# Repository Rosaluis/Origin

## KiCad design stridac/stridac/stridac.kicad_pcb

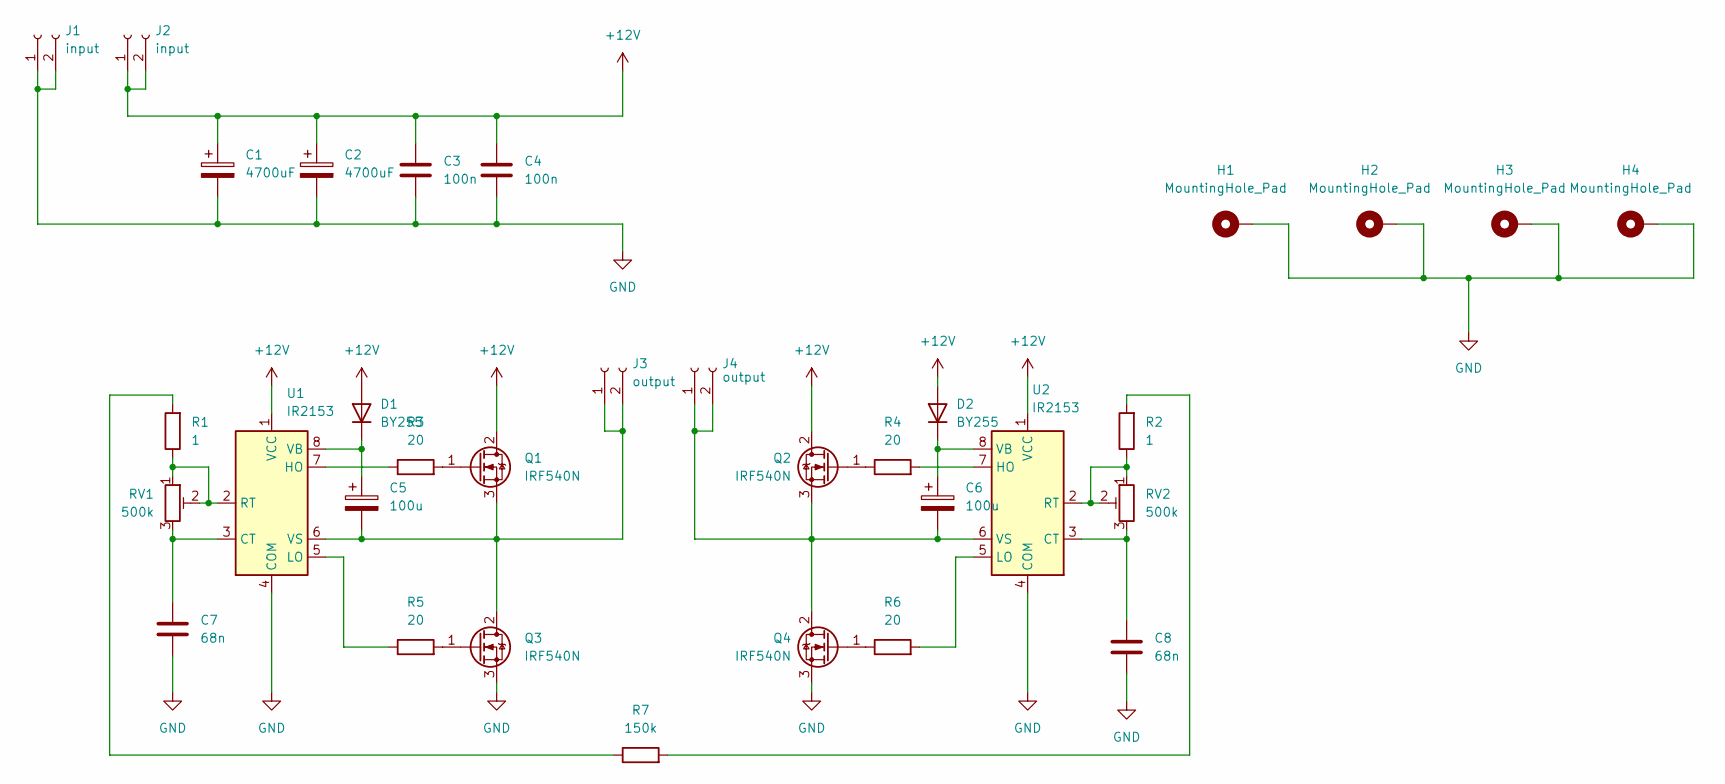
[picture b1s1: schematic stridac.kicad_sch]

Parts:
C1, C2: 4700uF; CP_Radial_D17.0mm_P7.50mm
C3, C4: 100n; C_1206_3216Metric_Pad1.33x1.80mm_HandSolder
C5, C6: 100u; CP_Radial_D8.0mm_P3.50mm
C7, C8: 68n; C_0805_2012Metric_Pad1.18x1.45mm_HandSolder
D1, D2: BY255; D_A-405_P10.16mm_Horizontal
H1, H2, H3, H4: MountingHole_Pad; MountingHole_3.2mm_M3_DIN965_Pad
J1, J2: input; PinHeader_1x02_P2.54mm_Vertical
J3, J4: output; PinHeader_1x02_P2.54mm_Vertical
Q1, Q2, Q3, Q4: IRF540N; TO-220-3_Vertical
R1, R2: 1; R_1206
R3, R4, R5, R6: 20; R_1206
R7: 150k; R_1206
RV1, RV2: 500k; Potentiometer_Vishay_T73XW_Horizontal
U1, U2: IR2153; DIP-8_W7.62mm

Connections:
+12V: C1.1, C2.1, C3.1, C4.1, D1.2 (A), D2.2 (A), J2.1, J2.2, Q1.2 (D), Q2.2 (D), U1.1 (VCC), U2.1 (VCC)
GND: C1.2, C2.2, C3.2, C4.2, C7.2, C8.2, H1.1, H2.1, H3.1, H4.1, J1.1, J1.2, Q3.3 (S), Q4.3 (S), U1.4 (COM), U2.4 (COM)
unnamed: C5.1, D1.1 (K), U1.8 (VB)
unnamed: C5.2, J3.1, J3.2, Q1.3 (S), Q3.2 (D), U1.6 (VS)
unnamed: C6.1, D2.1 (K), U2.8 (VB)
unnamed: C6.2, J4.1, J4.2, Q2.3 (S), Q4.2 (D), U2.6 (VS)
unnamed: C7.1, RV1.3, U1.3 (CT)
unnamed: C8.1, RV2.3, U2.3 (CT)
unnamed: Q1.1 (G), R3.2
unnamed: Q2.1 (G), R4.1
unnamed: Q3.1 (G), R5.2
unnamed: Q4.1 (G), R6.1
unnamed: R1.1, RV1.1, RV1.2, U1.2 (RT)
unnamed: R1.2, R7.1
unnamed: R2.1, RV2.1, RV2.2, U2.2 (RT)
unnamed: R2.2, R7.2
unnamed: R3.1, U1.7 (HO)
unnamed: R4.2, U2.7 (HO)
unnamed: R5.1, U1.5 (LO)
unnamed: R6.2, U2.5 (LO)

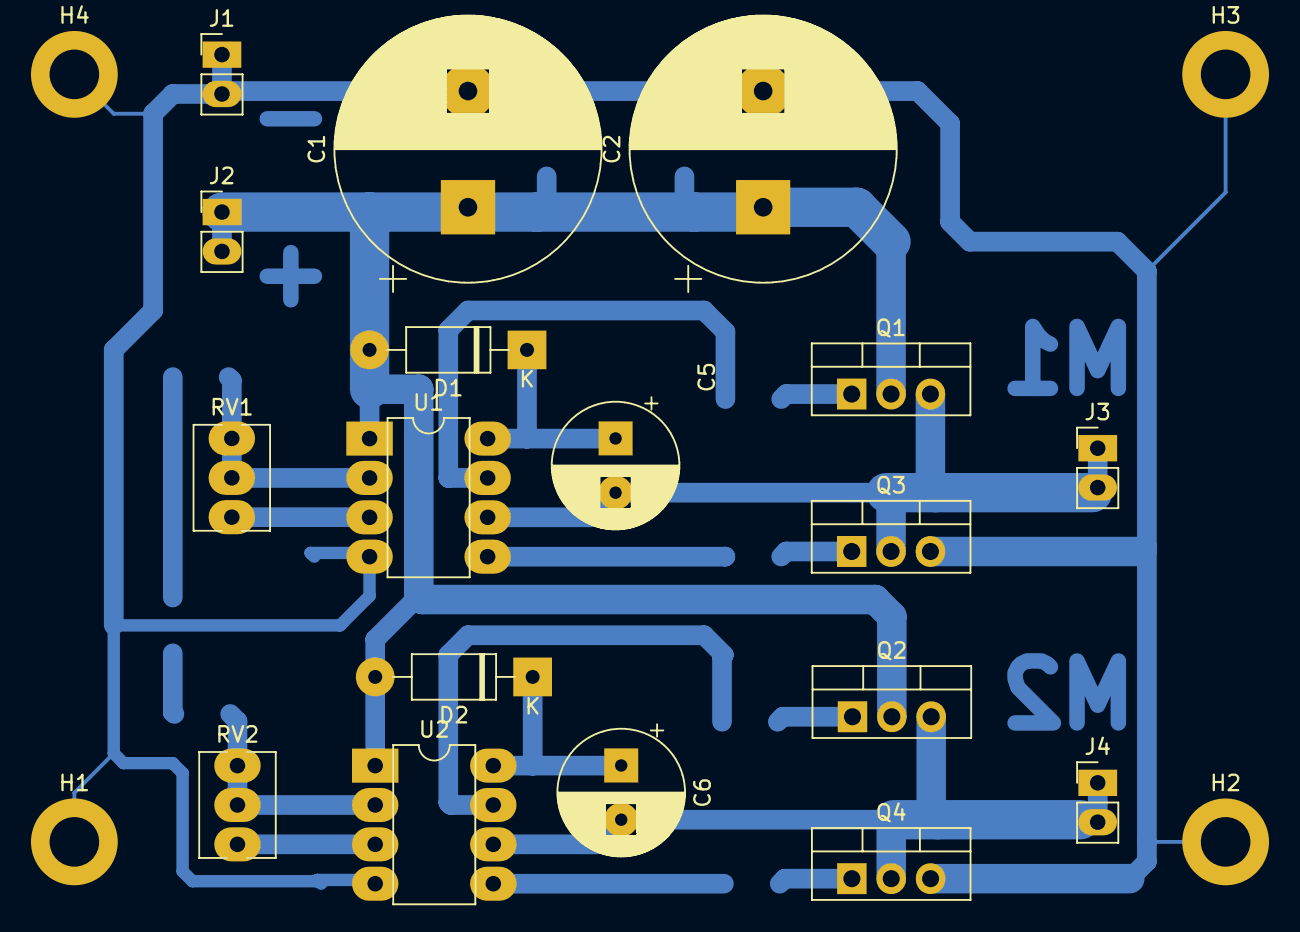
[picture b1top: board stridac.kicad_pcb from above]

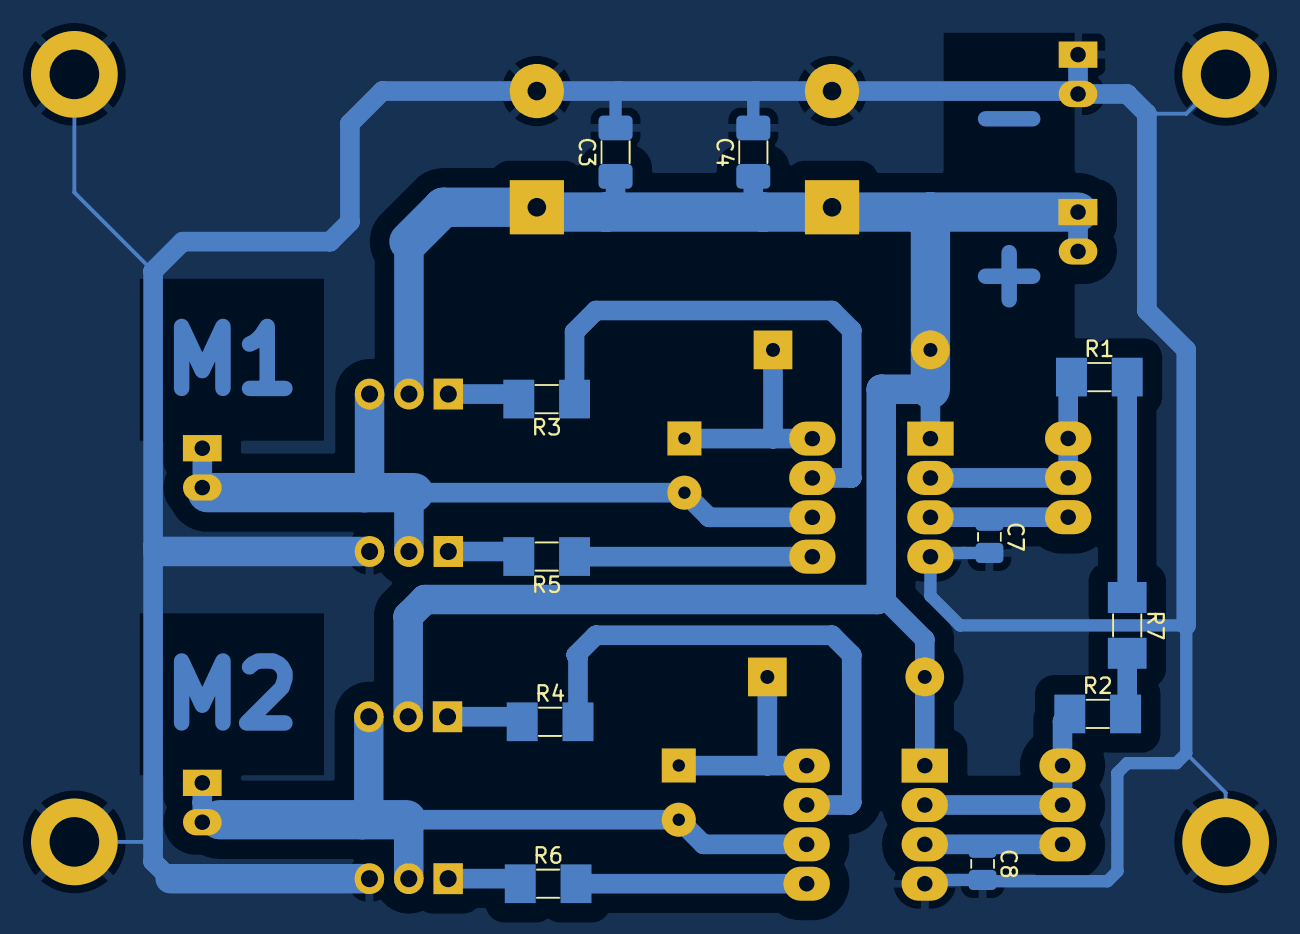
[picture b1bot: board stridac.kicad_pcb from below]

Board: 2 copper layers, 33 parts (11 on the bottom side), 20 nets.

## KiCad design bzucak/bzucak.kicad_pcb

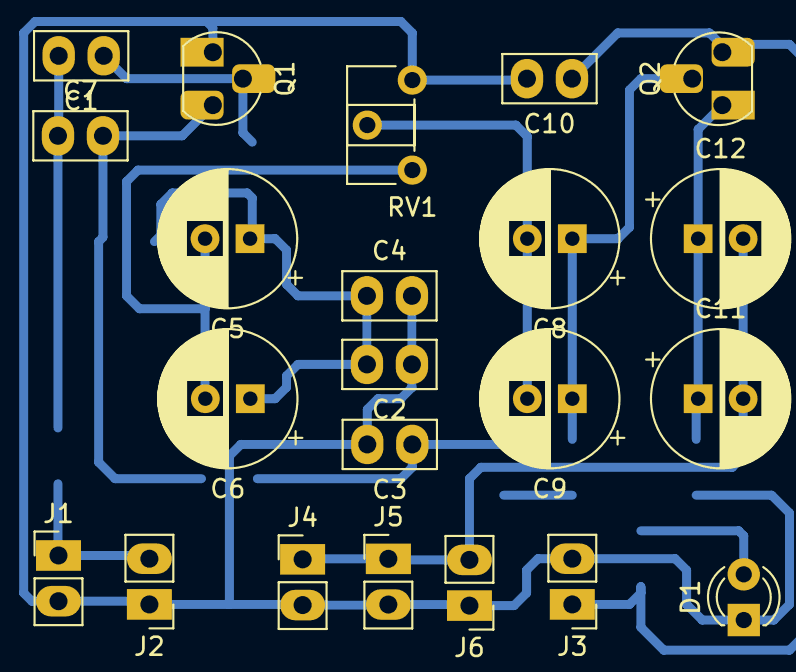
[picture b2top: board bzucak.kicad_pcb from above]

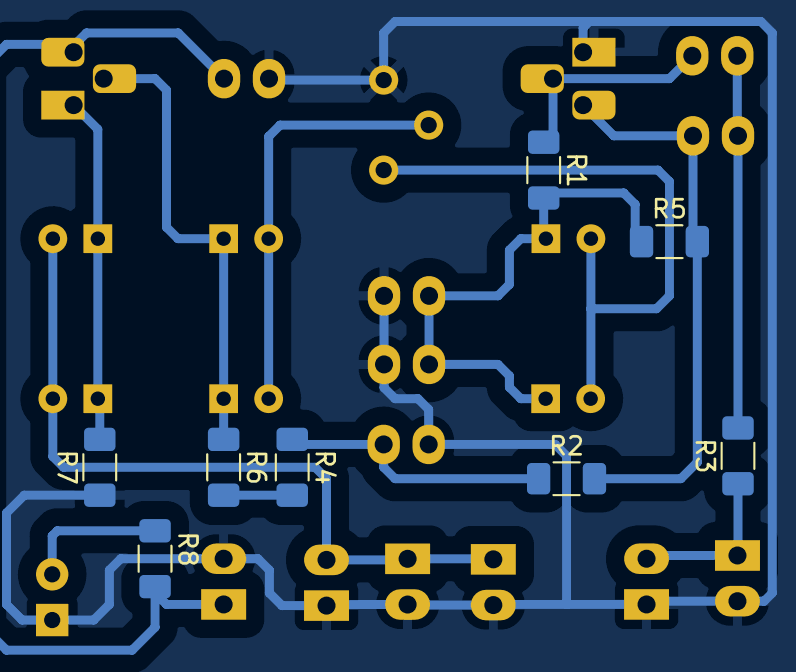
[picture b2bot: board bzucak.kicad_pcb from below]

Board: 2 copper layers, 30 parts (8 on the bottom side), 15 nets.

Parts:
C1, C2, C3, C4, C7, C10: 100n; C_Disc_D5.0mm_W2.5mm_P2.50mm
C5, C6, C8, C9, C11, C12: 10M; CP_Radial_D7.5mm_P2.50mm
D1: LED; LED_D3.0mm
J1: key; PinHeader_1x02_P2.54mm_Vertical
J2: in_key; PinHeader_1x02_P2.54mm_Vertical
J3: power; PinHeader_1x02_P2.54mm_Vertical
J4: out_1; PinHeader_1x02_P2.54mm_Vertical
J5: out_2; PinHeader_1x02_P2.54mm_Vertical
J6: out_3; PinHeader_1x02_P2.54mm_Vertical
Q1, Q2: PN2222A; TO-92L_HandSolder
R1, R2, R5: 3k3; R_1206_3216Metric_Pad1.30x1.75mm_HandSolder
R3: 560; R_1206_3216Metric_Pad1.30x1.75mm_HandSolder
R4: 10; R_1206_3216Metric_Pad1.30x1.75mm_HandSolder
R6: 150k; R_1206_3216Metric_Pad1.30x1.75mm_HandSolder
R7: 100; R_1206_3216Metric_Pad1.30x1.75mm_HandSolder
R8: 1k; R_1206_3216Metric_Pad1.30x1.75mm_HandSolder
RV1: 10k; Potentiometer_Piher_PT-6-H_Horizontal

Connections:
GND: C2.1, C3.2, C4.2, C10.2, D1.1 (K), J1.2, J2.1, J3.2, J4.2, J5.2, J6.1, Q1.1 (E), R7.1, RV1.3
unnamed: C1.1, Q1.2 (B), R1.1
unnamed: C1.2, C7.1, R3.2
unnamed: C2.2, C4.1, C5.1, C6.1, R1.2, R5.1
unnamed: C3.1, R2.1, R4.1
unnamed: C5.2, C6.2, RV1.1
unnamed: C7.2, Q1.3 (C), R2.2, R5.2
unnamed: C8.1, C9.1, Q2.2 (B), R6.1
unnamed: C8.2, C9.2, RV1.2
unnamed: C10.1, J3.1, Q2.3 (C), R8.2
unnamed: C11.1, C12.1, Q2.1 (E), R7.2
unnamed: C11.2, C12.2, J4.1, J5.1, J6.2
unnamed: D1.2 (A), R8.1
unnamed: J1.1, J2.2, R3.1
unnamed: R4.2, R6.2

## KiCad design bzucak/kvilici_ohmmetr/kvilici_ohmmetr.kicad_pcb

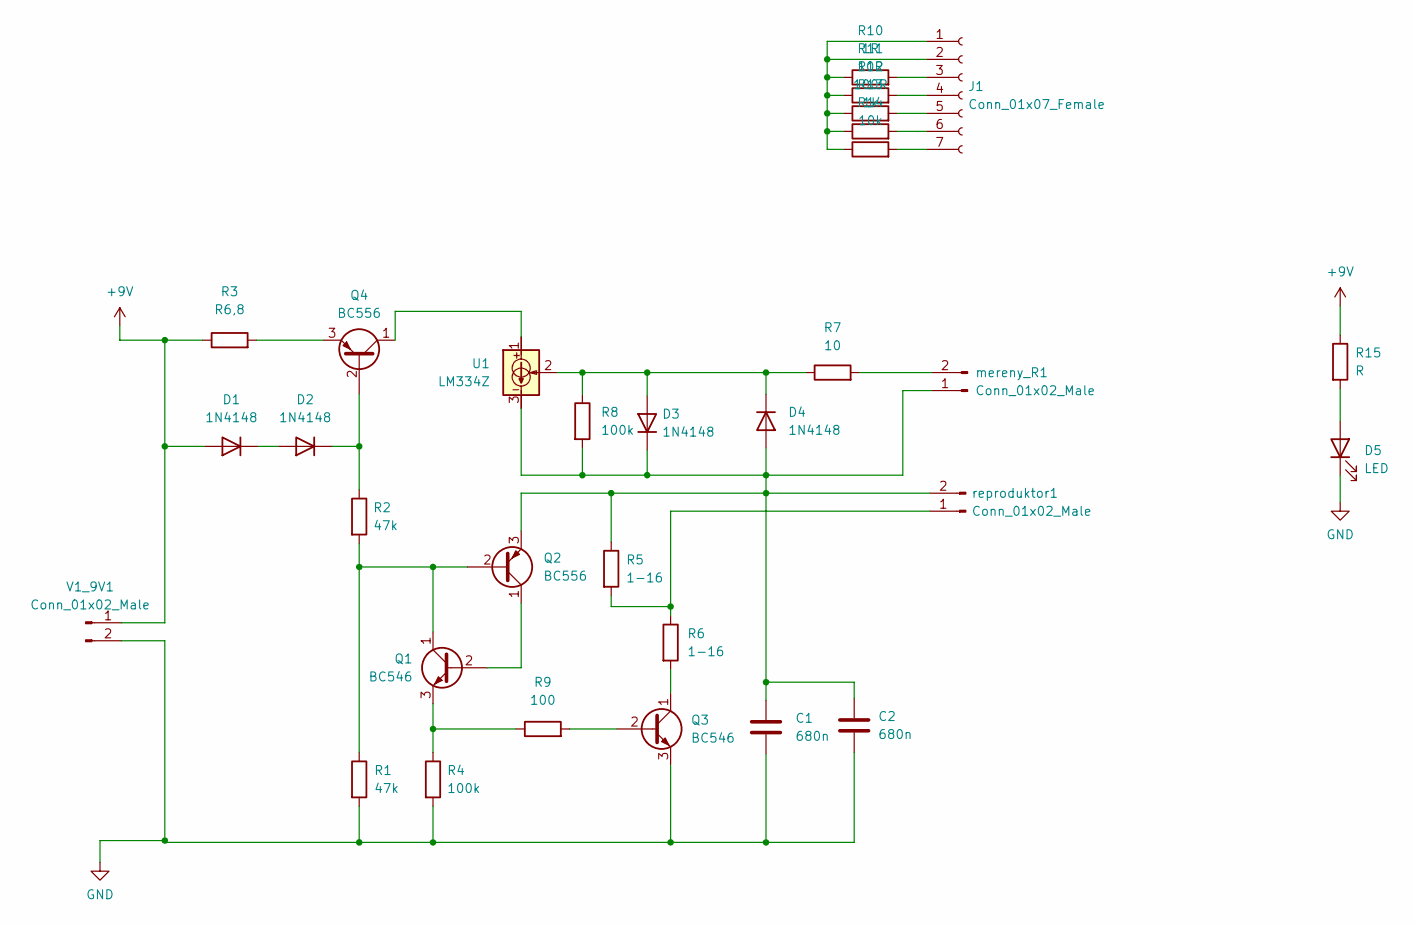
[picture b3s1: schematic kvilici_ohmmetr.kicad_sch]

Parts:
C1, C2: 680n; PinHeader_1x02_P2.54mm_Vertical
D1, D2, D3, D4: 1N4148; D_DO-35_SOD27_P7.62mm_Horizontal
D5: LED; LED_D3.0mm
J1: Conn_01x07_Female; PinHeader_1x07_P2.54mm_Vertical
Q1, Q3: BC546; TO-92
Q2, Q4: BC556; TO-92
R1, R2: 47k; R_1206
R3: R6,8; R_1206
R4, R8: 100k; R_1206
R5, R6: 1-16; R_1206
R7: 10; R_1206
R9: 100; R_1206
R10: 1R; R_1206
R11: 10R; R_1206
R12: 100R; R_1206
R13: 1k; R_1206
R14: 10k; R_1206
R15: R; R_1206
U1: LM334Z; TO-92
V1_9V1: Conn_01x02_Male; PinHeader_1x02_P2.54mm_Vertical
mereny_R1: Conn_01x02_Male; PinHeader_1x02_P2.54mm_Vertical
reproduktor1: Conn_01x02_Male; PinHeader_1x02_P2.54mm_Vertical

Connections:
+9V: D1.2 (A), R3.1, R15.1, V1_9V1.1
GND: C1.2, C2.2, D5.1 (K), Q3.3 (E), R1.2, R4.2, V1_9V1.2
unnamed: C1.1, C2.1, D3.1 (K), D4.2 (A), Q2.3 (E), R5.1, R8.2, U1.3, mereny_R1.1, reproduktor1.2
unnamed: D1.1 (K), D2.2 (A)
unnamed: D2.1 (K), Q4.2 (B), R2.1
unnamed: D3.2 (A), D4.1 (K), R7.1, R8.1, U1.2
unnamed: D5.2 (A), R15.2
unnamed: J1.1, J1.2, R10.1, R11.1, R12.1, R13.1, R14.1
unnamed: J1.3, R10.2
unnamed: J1.4, R11.2
unnamed: J1.5, R12.2
unnamed: J1.6, R13.2
unnamed: J1.7, R14.2
unnamed: Q1.1 (C), Q2.2 (B), R1.1, R2.2
unnamed: Q1.2 (B), Q2.1 (C)
unnamed: Q1.3 (E), R4.1, R9.1
unnamed: Q3.1 (C), R6.2
unnamed: Q3.2 (B), R9.2
unnamed: Q4.1 (C), U1.1
unnamed: Q4.3 (E), R3.2
unnamed: R5.2, R6.1, reproduktor1.1
unnamed: R7.2, mereny_R1.2

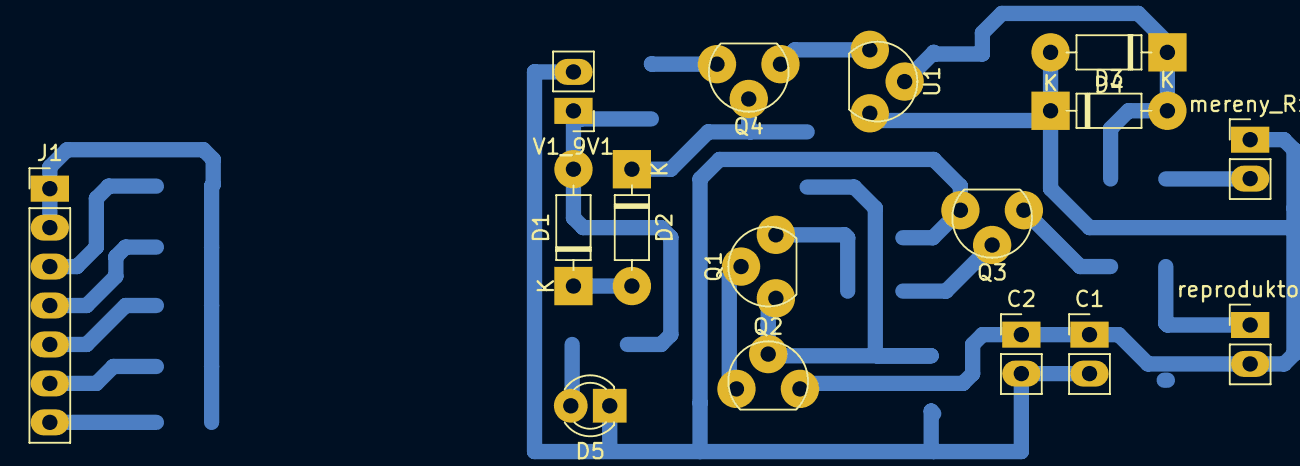
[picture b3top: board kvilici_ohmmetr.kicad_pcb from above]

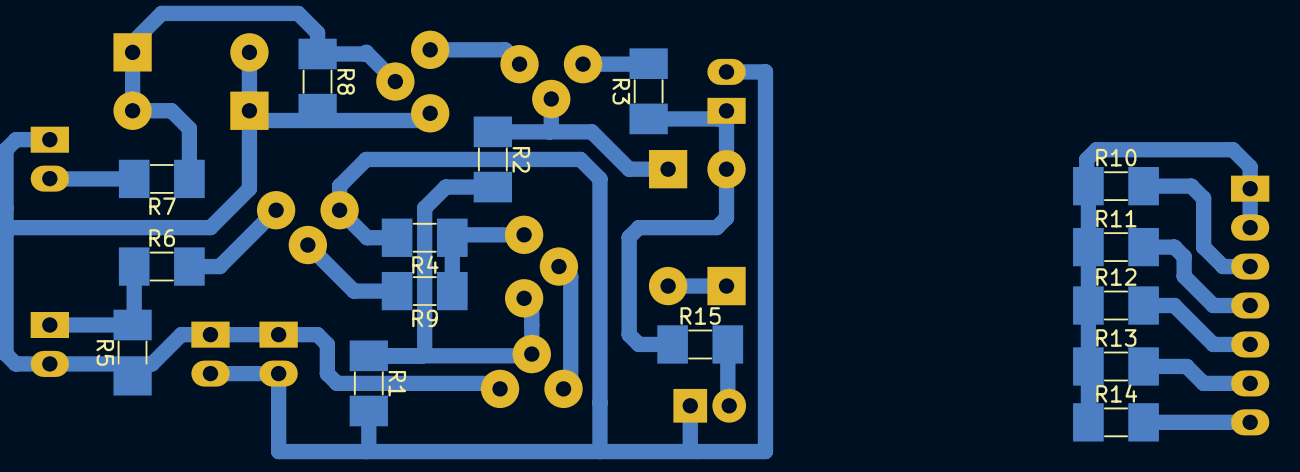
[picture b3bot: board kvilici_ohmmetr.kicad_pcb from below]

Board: 2 copper layers, 31 parts (15 on the bottom side), 22 nets.

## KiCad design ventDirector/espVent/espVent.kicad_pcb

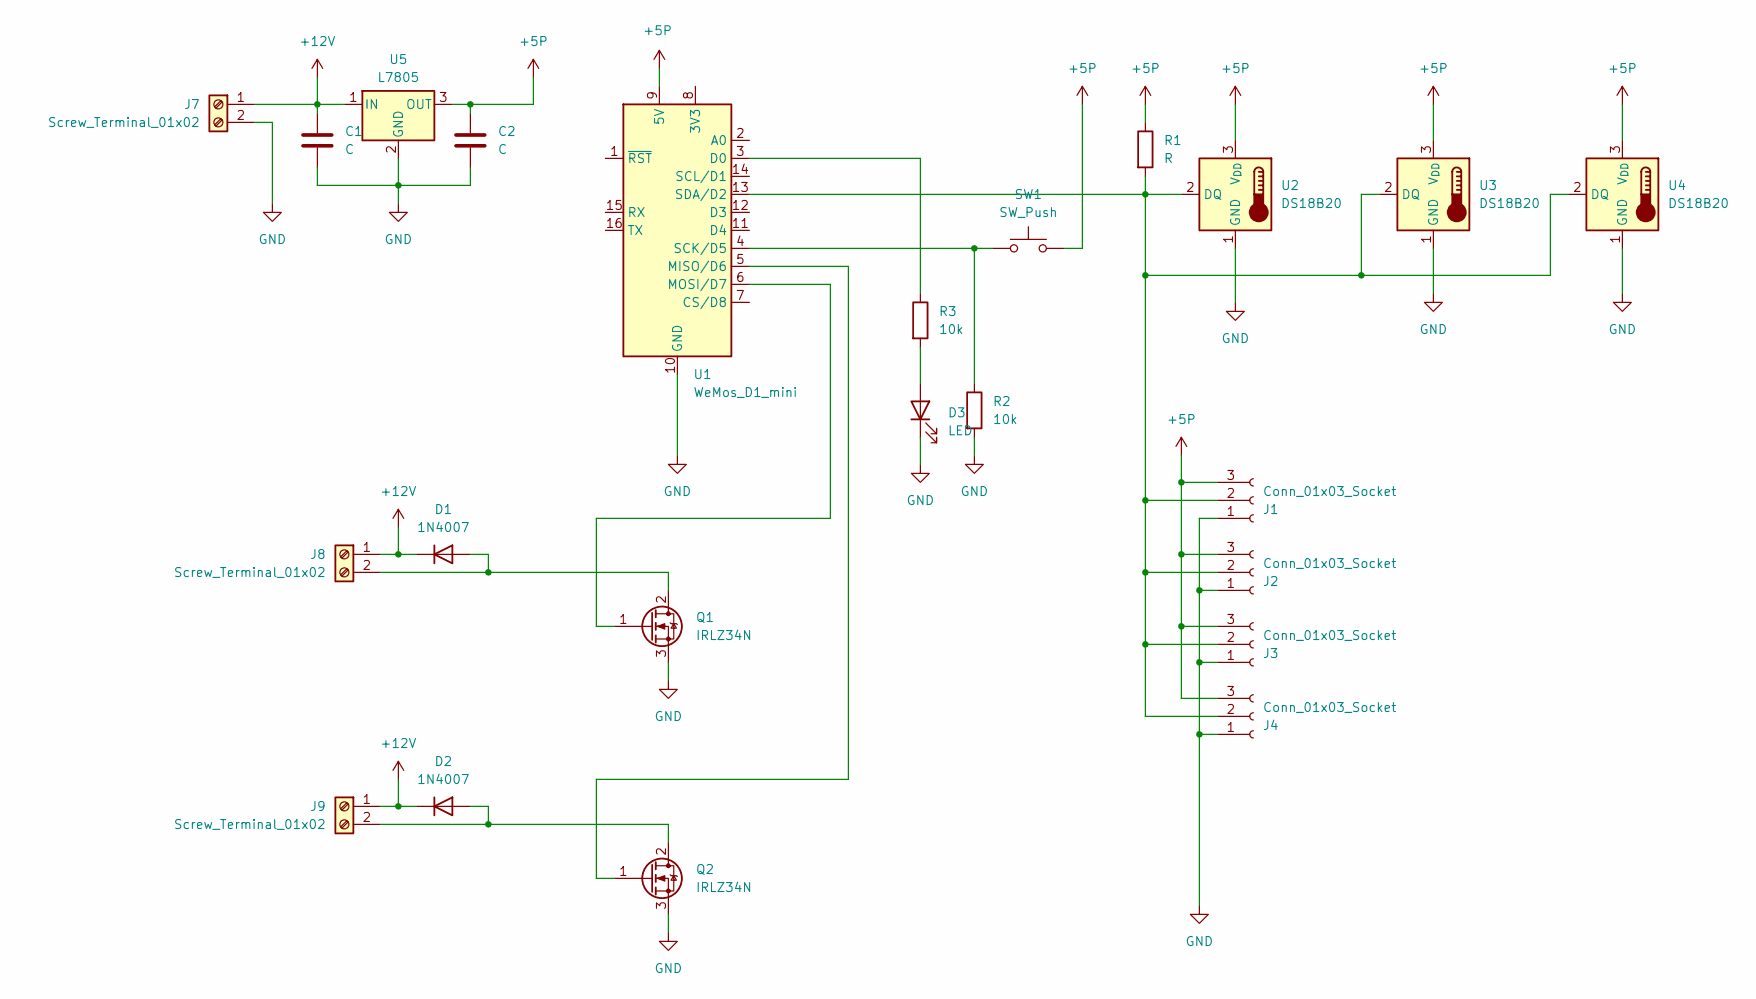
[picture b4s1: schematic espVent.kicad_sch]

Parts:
C1, C2: C; C_Disc_D5.0mm_W2.5mm_P2.50mm
D1, D2: 1N4007; D_DO-41_SOD81_P10.16mm_Horizontal
D3: LED; LED_D5.0mm
J1, J2, J3, J4: Conn_01x03_Socket; PinSocket_1x03_P2.54mm_Vertical
J7, J8, J9: Screw_Terminal_01x02; PinHeader_1x02_P2.54mm_Vertical
Q1, Q2: IRLZ34N; TO-220-3_Vertical
R1: R; R_Axial_DIN0207_L6.3mm_D2.5mm_P10.16mm_Horizontal
R2, R3: 10k; R_Axial_DIN0207_L6.3mm_D2.5mm_P10.16mm_Horizontal
SW1: SW_Push; SW_PUSH_6mm
U1: WeMos_D1_mini; ESP8266_WEMOS_D1
U2, U3, U4: DS18B20; TO-92_Inline
U5: L7805; TO-220-3_Vertical

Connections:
+5P: C2.1, J1.3, J2.3, J3.3, J4.3, R1.1, SW1.2, U1.9 (5V), U2.3 (V_{DD}), U3.3 (V_{DD}), U4.3 (V_{DD}), U5.3 (OUT)
+12V: C1.1, D1.1 (K), D2.1 (K), J7.1, J8.1, J9.1, U5.1 (IN)
GND: C1.2, C2.2, D3.1 (K), J1.1, J2.1, J3.1, J4.1, J7.2, Q1.3 (S), Q2.3 (S), R2.2, U1.10 (GND), U2.1 (GND), U3.1 (GND), U4.1 (GND), U5.2 (GND)
unnamed: D1.2 (A), J8.2, Q1.2 (D)
unnamed: D2.2 (A), J9.2, Q2.2 (D)
unnamed: D3.2 (A), R3.2
unnamed: J1.2, J2.2, J3.2, J4.2, R1.2, U1.13 (SDA/D2), U2.2 (DQ), U3.2 (DQ), U4.2 (DQ)
unnamed: Q1.1 (G), U1.6 (MOSI/D7)
unnamed: Q2.1 (G), U1.5 (MISO/D6)
unnamed: R3.1, U1.3 (D0)
unnamed: R2.1, SW1.1, U1.4 (SCK/D5)

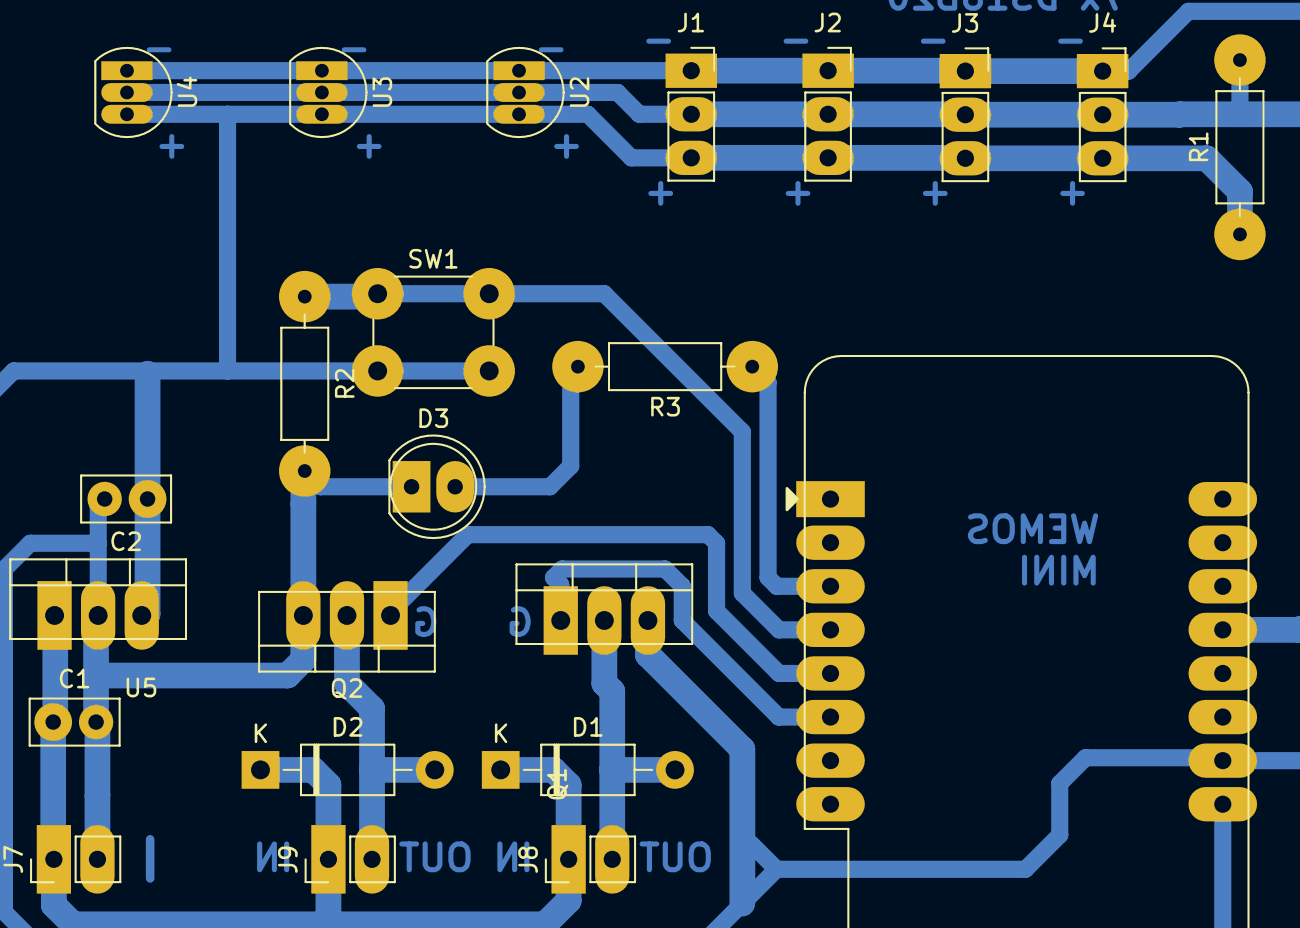
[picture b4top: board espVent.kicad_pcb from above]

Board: 2 copper layers, 23 parts (0 on the bottom side), 11 nets.

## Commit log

2024-04-01 Create test.txt
    testing
2024-04-01 First kiCAD project to git.
2024-04-01 My parts library.
2024-04-01 Realizovaný a funkční projekt - kvílící ohmmetr.
2024-04-01 I2C scanner for arduino.
2024-04-01 Realizovaný projekt střídače - ss na st U.
2024-04-01 Color balls sorter.
